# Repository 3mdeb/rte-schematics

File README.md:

Schematics for RTE system
=========================

This repository contains source files for Remote Testing Environment schematics.

If you want to read more about this project, here are some useful links:

* Firmware/software:
  - [meta-rte](https://github.com/3mdeb/meta-rte) - custom firmware for OrangePi
  Zero ([MIT license](https://github.com/3mdeb/meta-rte/blob/master/COPYING.MIT))
  - [RteCtrl](https://github.com/3mdeb/RteCtrl) - binary for power management on
  board ([MIT license](https://github.com/3mdeb/RteCtrl/blob/master/LICENSE))
* Datasheets (under CC BY-SA 4.0 International License):
  - [RTE v1.0.0 datasheet](https://cloud.3mdeb.com/index.php/s/NQCAHopjSpMGT9z)
  - [RTE v1.1.0 datasheet](https://docs.dasharo.com/transparent-validation/rte/v1.1.0/specification/)

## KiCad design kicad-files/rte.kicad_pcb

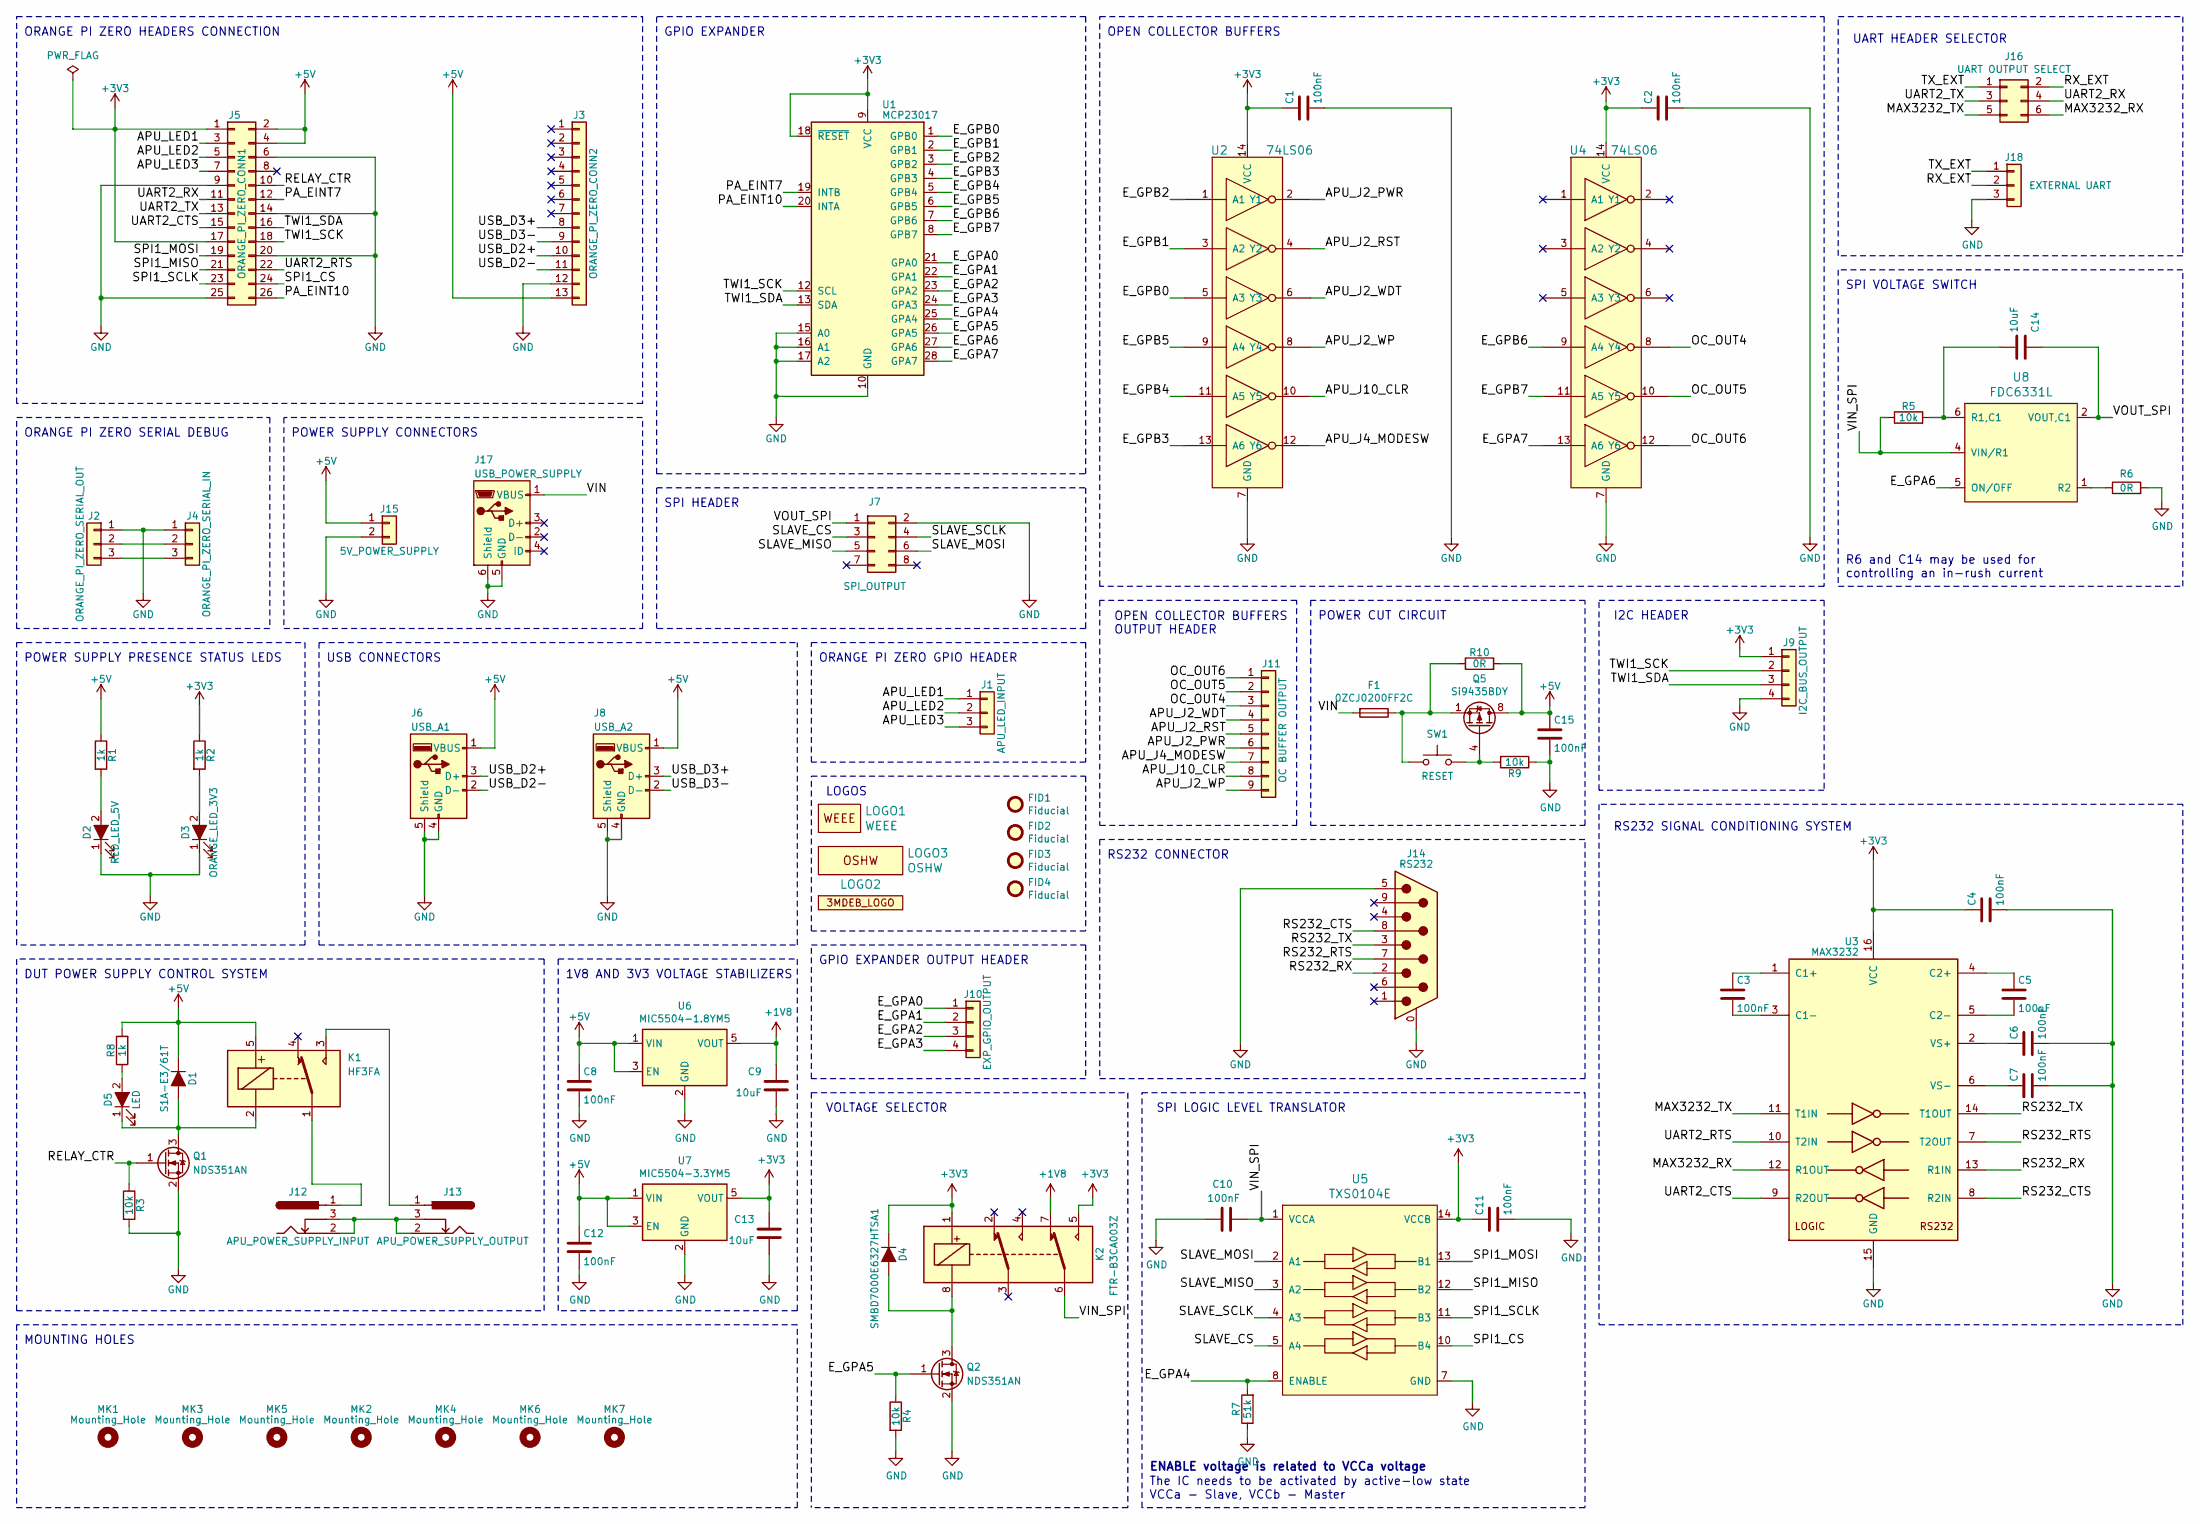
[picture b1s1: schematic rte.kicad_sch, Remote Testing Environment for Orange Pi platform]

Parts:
C1, C2, C3, C4, C5, C6, C7, C8, C10, C11, C12, C15: 100nF; C_0805_2012Metric; Voltage 50V
C9, C13, C14: 10uF; C_0805_2012Metric; Voltage 10V
D1: S1A-E3/61T; D_SMA; Voltage 50V
D2: RED_LED_5V; LED_1206_3216Metric
D3: ORANGE_LED_3V3; LED_1206_3216Metric
D4: SMBD7000E6327HTSA1; D_SOT-23_ANK
D5: LED; LED_1206_3216Metric
F1: 0ZCJ0200FF2C; Fuse_1206_3216Metric
FID1, FID2, FID3, FID4: Fiducial; Fiducial_0.75mm_Mask2.25mm
J1: APU_LED_INPUT; PinHeader_1x03_P2.54mm_Vertical
J2: ORANGE_PI_ZERO_SERIAL_OUT; PinHeader_1x03_P2.54mm_Vertical
J3: ORANGE_PI_ZERO_CONN2; PinSocket_1x13_P2.54mm_Vertical
J4: ORANGE_PI_ZERO_SERIAL_IN; PinSocket_1x03_P2.54mm_Vertical
J5: ORANGE_PI_ZERO_CONN1; PinSocket_2x13_P2.54mm_Vertical
J6: USB_A1; USB_A_Vertical
J7: SPI_OUTPUT; PinHeader_2x04_P2.54mm_Vertical
J8: USB_A2; USB_A_Vertical
J9: I2C_BUS_OUTPUT; PinHeader_1x04_P2.54mm_Vertical
J10: EXP_GPIO_OUTPUT; PinHeader_1x04_P2.54mm_Vertical
J11: OC BUFFER OUTPUT; PinHeader_1x09_P2.54mm_Vertical
J12: APU_POWER_SUPPLY_INPUT; BarrelJack_Horizontal
J13: APU_POWER_SUPPLY_OUTPUT; BarrelJack_Horizontal
J14: RS232; DB9MD
J15: 5V_POWER_SUPPLY; PinHeader_1x02_P2.54mm_Vertical
J16: UART OUTPUT SELECT; PinHeader_2x03_P2.54mm_Vertical
J17: USB_POWER_SUPPLY; USB_Micro-B
J18: EXTERNAL UART; PinHeader_1x03_P2.54mm_Vertical
K1: HF3FA; Relay_SPDT_SANYOU_SRD_Series_Form_C; Voltage 5V
K2: FTR-B3CA003Z; Relay_DPDT_AXICOM_IMSeries_Pitch5.08mm
LOGO1: WEEE; WEEE-Logo_4.2x6mm_SilkScreen
LOGO2: 3MDEB_LOGO; 3mdeb_logo
LOGO3: OSHW; OSHW-Logo2_7.3x6mm_SilkScreen
MK1, MK2, MK3, MK4, MK5, MK6, MK7: Mounting_Hole; MountingHole_2.7mm_Pad
Q1, Q2: NDS351AN; TSOT-23; Voltage 30V
Q5: Si9435BDY; SO-8_5.3x6.2mm_P1.27mm
R1, R2: 1k; R_1206_3216Metric
R3, R4, R5, R9: 10k; R_0805_2012Metric
R6: 0R; R_0805_2012Metric
R7: 51k; R_0805_2012Metric; Voltage 50V
R8: 1k; R_0805_2012Metric
R10: 0R; R_1206_3216Metric
SW1: RESET; SW_SPST_PTS645
U1: MCP23017; SOIC-28W_7.5x17.9mm_P1.27mm
U2, U4: 74LS06; SOIC-14_3.9x8.7mm_P1.27mm
U3: MAX3232; SOIC-16_3.9x9.9mm_P1.27mm
U5: TXS0104E; TSSOP-14_4.4x5mm_P0.65mm
U6: MIC5504-1.8YM5; SOT-23-5
U7: MIC5504-3.3YM5; SOT-23-5
U8: FDC6331L; SuperSOT-6

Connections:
+1V8: C9.2, K2.7, U6.5 (VOUT)
+3V3: C1.1, C2.1, C4.1, C11.1, C13.2, D4.1 (K), J5.1, J5.17, J9.1, K2.1, K2.5, R2.1, U1.9 (VCC), U1.18 (~RESET), U2.14 (VCC), U3.16 (VCC), U4.14 (VCC), U5.14 (VCCB), U7.5 (VOUT)
+5V: C8.1, C12.1, C15.1, D1.1 (K), J3.13, J5.2, J5.4, J6.1 (VBUS), J8.1 (VBUS), J15.1, K1.5, Q5.5 (D), Q5.6 (D), Q5.7 (D), Q5.8 (D), R1.1, R8.2, R10.2, U6.1 (VIN), U6.3 (EN), U7.1 (VIN), U7.3 (EN)
/APU_J2_PWR: J11.6, U2.2 (Y1)
/APU_J2_RST: J11.5, U2.4 (Y2)
/APU_J2_WDT: J11.4, U2.6 (Y3)
/APU_J2_WP: J11.9, U2.8 (Y4)
/APU_J4_MODESW: J11.7, U2.12 (Y6)
/APU_J10_CLR: J11.8, U2.10 (Y5)
/APU_LED1: J1.1, J5.3
/APU_LED2: J1.2, J5.5
/APU_LED3: J1.3, J5.7
/E_GPA0: J10.1, U1.21 (GPA0)
/E_GPA1: J10.2, U1.22 (GPA1)
/E_GPA2: J10.3, U1.23 (GPA2)
/E_GPA3: J10.4, U1.24 (GPA3)
/E_GPA4: R7.2, U1.25 (GPA4), U5.8 (ENABLE)
/E_GPA5: Q2.1 (G), R4.1, U1.26 (GPA5)
/E_GPA6: U1.27 (GPA6), U8.5 (ON/OFF)
/E_GPA7: U1.28 (GPA7), U4.13 (A6)
/E_GPB0: U1.1 (GPB0), U2.5 (A3)
/E_GPB1: U1.2 (GPB1), U2.3 (A2)
/E_GPB2: U1.3 (GPB2), U2.1 (A1)
/E_GPB3: U1.4 (GPB3), U2.13 (A6)
/E_GPB4: U1.5 (GPB4), U2.11 (A5)
/E_GPB5: U1.6 (GPB5), U2.9 (A4)
/E_GPB6: U1.7 (GPB6), U4.9 (A4)
/E_GPB7: U1.8 (GPB7), U4.11 (A5)
/MAX3232_RX: J16.6, U3.12 (R1OUT)
/MAX3232_TX: J16.5, U3.11 (T1IN)
/OC_OUT4: J11.3, U4.8 (Y4)
/OC_OUT5: J11.2, U4.10 (Y5)
/OC_OUT6: J11.1, U4.12 (Y6)
/PA_EINT7: J5.12, U1.19 (INTB)
/PA_EINT10: J5.26, U1.20 (INTA)
/RELAY_CTR: J5.10, Q1.1 (G), R3.1
/RS232_CTS: J14.8, U3.8 (R2IN)
/RS232_RTS: J14.7, U3.7 (T2OUT)
/RS232_RX: J14.2, U3.13 (R1IN)
/RS232_TX: J14.3, U3.14 (T1OUT)
/RX_EXT: J16.2, J18.2
/SLAVE_CS: J7.3, U5.5 (A4)
/SLAVE_MISO: J7.5, U5.3 (A2)
/SLAVE_MOSI: J7.6, U5.2 (A1)
/SLAVE_SCLK: J7.4, U5.4 (A3)
/SPI1_CS: J5.24, U5.10 (B4)
/SPI1_MISO: J5.21, U5.12 (B2)
/SPI1_MOSI: J5.19, U5.13 (B1)
/SPI1_SCLK: J5.23, U5.11 (B3)
/TWI1_SCK: J5.18, J9.2, U1.12 (SCL)
/TWI1_SDA: J5.16, J9.3, U1.13 (SDA)
/TX_EXT: J16.1, J18.1
/UART2_CTS: J5.15, U3.9 (R2OUT)
/UART2_RTS: J5.22, U3.10 (T2IN)
/UART2_RX: J5.11, J16.4
/UART2_TX: J5.13, J16.3
/USB_D2+: J3.10, J6.3 (D+)
/USB_D2-: J3.11, J6.2 (D-)
/USB_D3+: J3.8, J8.3 (D+)
/USB_D3-: J3.9, J8.2 (D-)
/VIN: F1.2, J17.1 (VBUS)
/VIN_SPI: C10.2, K2.6, R5.1, U5.1 (VCCA), U8.4 (VIN/R1)
/VOUT_SPI: C14.2, J7.1, U8.2 (VOUT,C1), U8.3 (VOUT,C1)
GND: C1.2, C2.2, C4.2, C6.2, C7.2, C8.2, C9.1, C10.1, C11.2, C12.2, C13.1, C15.2, D2.1 (K), D3.1 (K), J2.1, J3.12, J4.1, J5.6, J5.9, J5.14, J5.20, J5.25, J6.4 (GND), J6.5 (Shield), J7.2, J8.4 (GND), J8.5 (Shield), J9.4, J14.0 (PAD), J14.5, J15.2, J17.5 (GND), J17.6 (Shield), J18.3, Q1.2 (S), Q2.2 (S), R3.2, R4.2, R6.2, R7.1, R9.1, U1.10 (GND), U1.15 (A0), U1.16 (A1), U1.17 (A2), U2.7 (GND), U3.15 (GND), U4.7 (GND), U5.7 (GND), U6.2 (GND), U7.2 (GND)
unnamed: C3.1, U3.1 (C1+)
unnamed: C3.2, U3.3 (C1-)
unnamed: C5.1, U3.4 (C2+)
unnamed: C5.2, U3.5 (C2-)
unnamed: C6.1, U3.2 (VS+)
unnamed: C7.1, U3.6 (VS-)
unnamed: C14.1, R5.2, U8.6 (R1,C1)
unnamed: D1.2 (A), D5.1 (K), K1.2, Q1.3 (D)
unnamed: D2.2 (A), R1.2
unnamed: D3.2 (A), R2.2
unnamed: D4.2 (A), K2.8, Q2.3 (D)
unnamed: D5.2 (A), R8.1
unnamed: F1.1, Q5.1 (S), Q5.2 (S), Q5.3 (S), R10.1, SW1.1
unnamed: J2.2, J4.2
unnamed: J2.3, J4.3
unnamed: J12.1, K1.1
unnamed: J12.2, J12.3, J13.2, J13.3
unnamed: J13.1, K1.3
unnamed: Q5.4 (G), R9.2, SW1.2
unnamed: R6.1, U8.1 (R2)

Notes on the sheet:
ORANGE PI ZERO HEADERS CONNECTION
UART HEADER SELECTOR
SPI HEADER
ORANGE PI ZERO GPIO HEADER
USB CONNECTORS
I2C HEADER
ENABLE voltage is related to VCCa voltage
LOGOS
VOLTAGE SELECTOR
1V8 AND 3V3 VOLTAGE STABILIZERS
POWER SUPPLY PRESENCE STATUS LEDS
RS232 SIGNAL CONDITIONING SYSTEM
GPIO EXPANDER
OPEN COLLECTOR BUFFERS OUTPUT HEADER
SPI VOLTAGE SWITCH
SPI LOGIC LEVEL TRANSLATOR
POWER CUT CIRCUIT
RS232 CONNECTOR
ORANGE PI ZERO SERIAL DEBUG
POWER SUPPLY CONNECTORS
MOUNTING HOLES
DUT POWER SUPPLY CONTROL SYSTEM
GPIO EXPANDER OUTPUT HEADER
OPEN COLLECTOR BUFFERS
The IC needs to be activated by active-low state VCCa - Slave, VCCb - Master
R6 and C14 may be used for controlling an in-rush current

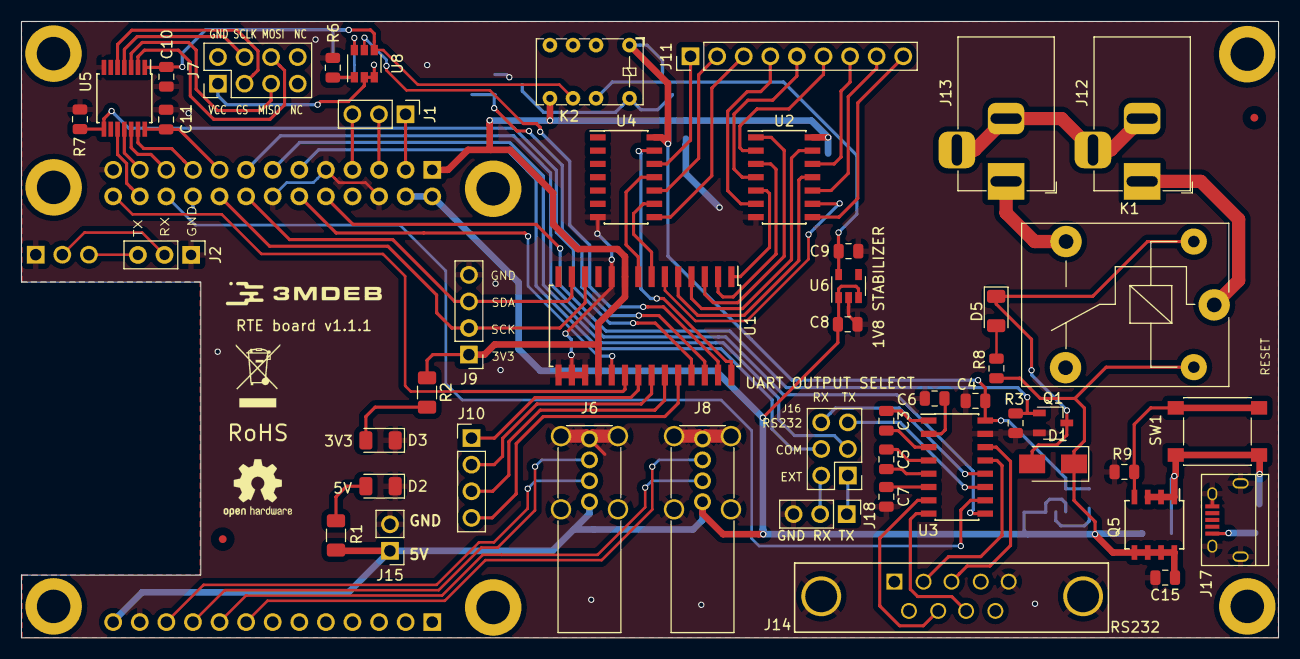
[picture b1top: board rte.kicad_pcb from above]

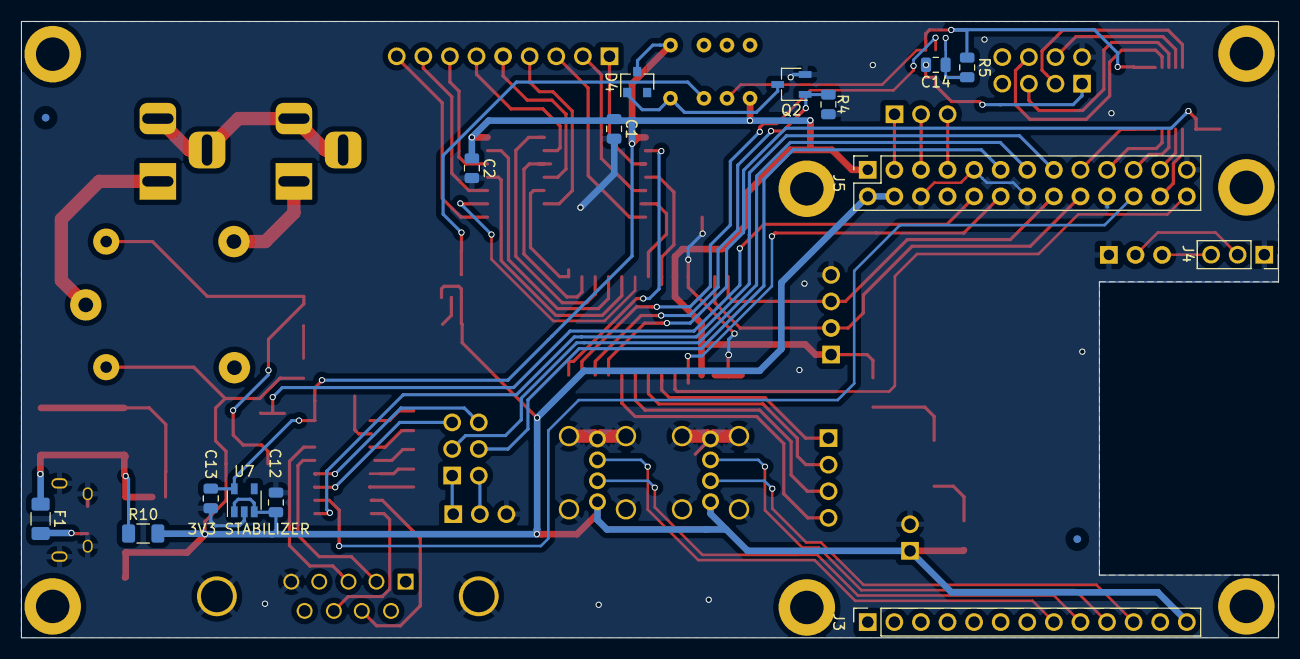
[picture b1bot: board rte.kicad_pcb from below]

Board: 2 copper layers, 120.1 x 58.9 mm, 77 parts (17 on the bottom side), 84 nets.

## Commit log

2018-04-02 RTE schematic and PCB uploaded
2019-04-03 Updated schematics to v1.0.0
2019-04-03 removed PlotDirectoryName
2019-04-19 CHANGELOG.md: reverse version order
2019-06-24 Updated schematic v1.1.0
2019-06-24 updated changelog
2019-06-24 added gitignore file
2019-06-24 added pdf schematic, removed backup files
2020-03-03 README.md: add resources and licensing info
2020-03-03 README.md: specify CC BY-SA license
2021-06-09 README.md: fix incorrect links
2024-07-11 Update Q5 footprint to match the Si9435BDY recommended footprint
2024-07-11 Refactor USB data lines to be more equal in length
2024-07-11 kicad-files/rte.kicad_pcb: Change board version to v1.1.1
2024-07-11 kicad-files/rte.kicad_pro: Add new format of project file
2024-07-11 kicad-files/rte.kicad_sch: Add new format of schematics file
